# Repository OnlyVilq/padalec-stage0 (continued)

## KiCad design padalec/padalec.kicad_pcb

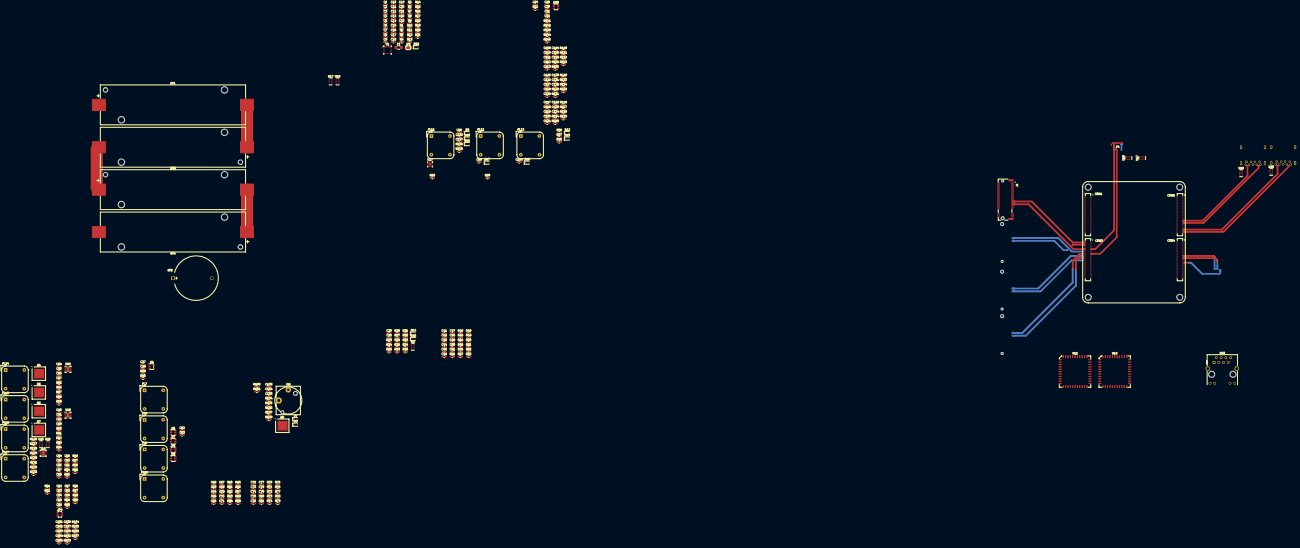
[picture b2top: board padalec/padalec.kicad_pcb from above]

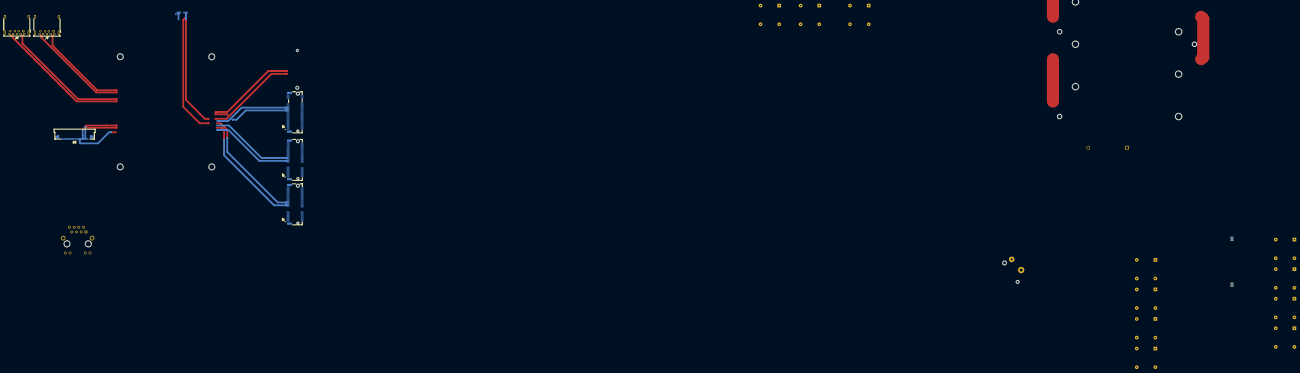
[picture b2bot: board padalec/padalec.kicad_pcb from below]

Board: 4 copper layers, 343 parts (6 on the bottom side), 225 nets.

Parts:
BT1, BT2, BT3, BT4: Battery_Cell; BatteryHolder_Keystone_1042_1x18650
BT5: Battery_Cell; BatteryHolder_MYOUNG_BS-07-A1BJ001_CR2032
C1, C2, C7, C8, C11, C13, C15, C22, C23, C25, C54, C55, C63, C73, C82, C83, C90, C94, C101, C102, C109, C110, C117, C118, C125, C126: 10u; C_0603_1608Metric_Pad1.08x0.95mm_HandSolder
C3, C6, C52, C53, C57, C61, C85, C89, C91, C95, C98, C99, C100, C104, C108, C112, C116, C120, C124, C128, C132: 0.1u; C_0603_1608Metric_Pad1.08x0.95mm_HandSolder
C4, C5: 47n; C_0603_1608Metric_Pad1.08x0.95mm_HandSolder
C9, C41: 1n; C_0603_1608Metric_Pad1.08x0.95mm_HandSolder
C10, C27, C28, C48, C50, C51: 4.7u; C_0603_1608Metric_Pad1.08x0.95mm_HandSolder
C12, C14, C17, C18, C19, C20, C21, C29, C62, C64, C72, C74, C134: 1u; C_0603_1608Metric_Pad1.08x0.95mm_HandSolder
C16, C26, C31, C42, C43, C44, C45, C49, C56, C65, C68, C69, C70, C71, C75, C78, C79, C80, C81, C84, C103, C111, C119, C127, C133, C135: 100n; C_0603_1608Metric_Pad1.08x0.95mm_HandSolder
C24: 10n; C_0603_1608Metric_Pad1.08x0.95mm_HandSolder
C30: 2.2n; C_0603_1608Metric_Pad1.08x0.95mm_HandSolder
C32: 22n; C_0603_1608Metric_Pad1.08x0.95mm_HandSolder
C46, C47: 6p; C_0603_1608Metric_Pad1.08x0.95mm_HandSolder
C58, C105, C113, C121, C129: 2.2u; C_0603_1608Metric_Pad1.08x0.95mm_HandSolder
C59, C60, C87, C88, C106, C107, C114, C115, C122, C123, C130, C131: 22u; C_0603_1608Metric_Pad1.08x0.95mm_HandSolder
C66, C67, C76, C77: 6.8p; C_0603_1608Metric_Pad1.08x0.95mm_HandSolder
C86: 3.3u; C_0603_1608Metric_Pad1.08x0.95mm_HandSolder
C92, C93, C96, C97: 150u; C_0603_1608Metric_Pad1.08x0.95mm_HandSolder
C136, C137: 220p; C_0603_1608Metric_Pad1.08x0.95mm_HandSolder
D2: eDP_30pin; Amphenol_F32Q-1A7x1-11029_1x29-1MP_P0.5mm_Horizontal
D7, D8, D9, D10, D11, D12, D13, D14, D15, D16, D17, D18: PESD5V0X1BL; D_SOD-323
F1: Fuse; Fuse_1206_3216Metric_Pad1.42x1.75mm_HandSolder
FL7, FL8, FL9, FL10: Choke_Schaffner_RN102-04-14.0x14.0mm
FL11, FL12, FL13, FL14, FL15, FL16, FL17: DNP; Choke_Schaffner_RN102-04-14.0x14.0mm
J1: CM3588 Hirose Connector; CM3588
J4, J6: Bus_M.2_Socket_M; AMPHENOL_MDT420M03001
J5, J9: Bus_M.2_Socket_E; AMPHENOL_MDT420E03001
J7, J8: USB3_A; USB3_A_Molex_48393-001
J10: HDMI_A; WDFN-10-1EP_3x3mm_P0.5mm_EP1.8x2.5mm
J11: AudioJack3_SwitchTR; Jack_6.35mm_Neutrik_NJ2FD-V_Vertical
JP1: SolderJumper_2_Open; SolderJumper-2_P1.3mm_Open_RoundedPad1.0x1.5mm
JP4: 5v buck; SOT-23-6
P1: USB_C_Plug; USB_C_Plug_Molex_105444
Q4, Q5, Q6, Q7, Q8: NMOS; Nordic_AQFN-94-1EP_7x7mm_P0.4mm
R1, R134: 2.2k; R_0603_1608Metric_Pad0.98x0.95mm_HandSolder
R2, R38, R145: R_Small; R_0603_1608Metric_Pad0.98x0.95mm_HandSolder
R3: 30.31 k; R_0603_1608Metric_Pad0.98x0.95mm_HandSolder
R4, R22: 100; R_0603_1608Metric_Pad0.98x0.95mm_HandSolder
R5, R7, R9, R10, R11, R47, R48, R49, R50, R54, R56, R59, R61, R62, R63, R64, R65, R66, R67, R68, R69, R71, R72, R73, R74, R75, R76, R77, R78, R79, R81, R82, R84, R86, R89, R100, R101, R102, R104, R107, R108, R110, R113, R114, R116, R119, R120, R122, R125, R135, R137, R138, R144: 10k; R_0603_1608Metric_Pad0.98x0.95mm_HandSolder
R6: 470k; R_0603_1608Metric_Pad0.98x0.95mm_HandSolder
R8, R20: 1k; R_0603_1608Metric_Pad0.98x0.95mm_HandSolder
R12, R13, R14, R15, R16: 68; R_0603_1608Metric_Pad0.98x0.95mm_HandSolder
R17: 1m; R_0603_1608Metric_Pad0.98x0.95mm_HandSolder
R18, R21, R45: 1M; R_0603_1608Metric_Pad0.98x0.95mm_HandSolder
R19: 4k5; R_0603_1608Metric_Pad0.98x0.95mm_HandSolder
R23, R29, R30, R31, R32, R33: DNP; R_0603_1608Metric_Pad0.98x0.95mm_HandSolder
R24, R25, R26, R27, R28, R34, R35, R36, R37: 33; R_0603_1608Metric_Pad0.98x0.95mm_HandSolder
R39, R80, R83: 47k; R_0603_1608Metric_Pad0.98x0.95mm_HandSolder
R40, R46, R51, R52, R53, R55, R85, R90, R91, R93, R94, R95, R96, R98, R99, R103, R109, R115, R121, R136, R143: 100k; R_0603_1608Metric_Pad0.98x0.95mm_HandSolder
R41: 4.7k; R_0603_1608Metric_Pad0.98x0.95mm_HandSolder
R42: 0; R_0603_1608Metric_Pad0.98x0.95mm_HandSolder
R43: 10K; R_0603_1608Metric_Pad0.98x0.95mm_HandSolder
R44: 12K; R_0603_1608Metric_Pad0.98x0.95mm_HandSolder
R57, R87, R105, R111, R117, R123: 20k; R_0603_1608Metric_Pad0.98x0.95mm_HandSolder
R58, R106, R112, R118, R124: 45.3k; R_0603_1608Metric_Pad0.98x0.95mm_HandSolder
R60, R70: 1; R_0603_1608Metric_Pad0.98x0.95mm_HandSolder
R88: 73.2k; R_0603_1608Metric_Pad0.98x0.95mm_HandSolder
R92, R97: 37.4k; R_0603_1608Metric_Pad0.98x0.95mm_HandSolder
R126, R127, R128, R129, R130, R131, R132, R133: 499; R_0603_1608Metric_Pad0.98x0.95mm_HandSolder
R139, R140: 2.2K; R_0603_1608Metric_Pad0.98x0.95mm_HandSolder
R141: dnp; R_0603_1608Metric_Pad0.98x0.95mm_HandSolder
R142: 10; R_0603_1608Metric_Pad0.98x0.95mm_HandSolder
U1: BQ25798; Texas_RQM0029A_VQFN-29_4x4mm_P0.4mm
U3, U17, U17#2, U18, U18#2, U19, U20, U25, U26: TPD6E05U06RVZ; Texas_R-PUSON-N14
U4: MCP73831-2-OT; SOT-23-5
U6, U7, U8, U9: 82400102; SOT-23-6
U10: TMJUTVW0021192448; RJ45_Hanrun_HR911105A_Horizontal
U12, U13: 9FGV0441; PLCC-44_16.6x16.6mm_P1.27mm
U15, U16: TPS2561; VSON-10-1EP_3x3mm_P0.5mm_EP1.65x2.4mm_ThermalVias
U27: FUSB302BMPX; WQFN-14-1EP_2.5x2.5mm_P0.5mm_EP1.45x1.45mm
U28: TPS22810DBV; SOT-23-6

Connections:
+1V8: R23.1, R134.1, R136.1
+3V3: C29.1, R38.1, R42.1, R139.1, R140.1, U27.3 (VDD), U27.4 (VDD), U28.1 (VIN)
+5V: C27.1, C90.1, C91.1, C94.1, C95.1, JP4.2 (B), R93.1, R94.1, R98.1, R99.1, U4.4 (V_{DD}), U15.2 (IN), U15.3 (IN), U16.2 (IN), U16.3 (IN), U27.12 (VCONN), U27.13 (VCONN)
/Debug UART/RX: D12.2 (A2), R37.2, R38.2
/Debug UART/TX: D13.2 (A2), R36.2
/Debug UART/UART2_RX: J1.22, R37.1
/Debug UART/UART2_TX: J1.20, R36.1
/EDP 1/Bl_VCC: C32.2, D2.26 (Bl_VCC), D2.27 (Bl_VCC), D2.28 (Bl_VCC), D2.29 (Bl_VCC), R144.2
/EDP 1/LCD_VCC: C31.1, D2.12 (LCD_VCC), D2.13 (LCD_VCC), R141.2, R142.1, U28.6 (VOUT)
/EDP 1/eDP.AUX_N: D2.10 (AUX_N), J1.359
/EDP 1/eDP.AUX_P: D2.9 (AUX_P), J1.357
/EDP 1/eDP.TX0_N: D2.6 (TX0_N), J1.347
/EDP 1/eDP.TX0_P: D2.7 (TX0_P), J1.345
/EDP 1/eDP.TX1_N: D2.3 (TX1_N), J1.341
/EDP 1/eDP.TX1_P: D2.4 (TX1_P), J1.339
/Ethernet/Gled: C52.1, J1.72
/Ethernet/TD1_N: J1.80, U6.3
/Ethernet/TD1_P: J1.78, U6.1
/Ethernet/TD2_N: J1.86, U7.3
/Ethernet/TD2_P: J1.84, U7.1
/Ethernet/TD3_N: J1.92, U8.3
/Ethernet/TD3_P: J1.90, U8.1
/Ethernet/TD4_N: J1.98, U9.3
/Ethernet/TD4_P: J1.96, U9.1
/Ethernet/U10_4: FL7.3, U6.4
/Ethernet/U10_6: FL7.1, U6.6
/Ethernet/U11_4: FL8.3, FL9.3, U7.4
/Ethernet/U11_6: FL8.1, FL9.1, U7.6
/Ethernet/U12_4: FL10.3, U8.4
/Ethernet/U12_6: FL10.1, U8.6
/Ethernet/Yled: C53.1, J1.74
/HDMI_tx/D0+: FL16.2, J10.7 (D0+), U25.9 (D3+)
/HDMI_tx/D0-: FL16.4, J10.9 (D0-), U25.8 (D3-)
/HDMI_tx/D1+: FL15.2, J10.4 (D1+), U25.12 (D2+)
/HDMI_tx/D1-: FL15.4, J10.6 (D1-), U25.11 (D2-)
/HDMI_tx/D2+: FL14.2, J10.1 (D2+), U25.14 (D1+)
/HDMI_tx/D2-: FL14.4, J10.3 (D2-), U25.13 (D1-)
/HDMI_tx/HDMI.D0_N: FL16.3, R128.1
/HDMI_tx/HDMI.D0_P: FL16.1, R129.1
/HDMI_tx/HDMI.D1_N: FL15.3, R130.1
/HDMI_tx/HDMI.D1_P: FL15.1, R131.1
/HDMI_tx/HDMI.D2_N: FL14.3, R132.1
/HDMI_tx/HDMI.D2_P: FL14.1, R133.1
/HDMI_tx/HDMI.D3_N: FL17.3, R126.1
/HDMI_tx/HDMI.D3_P: FL17.1, R127.1
/Jack_35/DET: R136.2, R137.1
/Jack_35/HPL: C133.1, D7.2 (A2), J1.104, J11.T, R135.1
/Jack_35/HPR: C135.1, D8.2 (A2), J1.103, R138.1
/Jack_35/HP_DET: J1.108, R134.2
/PCIE/M2_E_x1/3v3: J5.2 (3.3V), J5.4 (3.3V), J5.72 (3.3V), J5.74 (3.3V), R81.1, R82.1
/PCIE/M2_E_x1/~W_DISABLE1: J5.56 (~W_DISABLE1), R81.2
/PCIE/M2_E_x1/~W_DISABLE2: J5.54 (~W_DISABLE2), R82.2
/PCIE/M2_E_x2/3v3: J9.2 (3.3V), J9.4 (3.3V), J9.72 (3.3V), J9.74 (3.3V), R100.1, R101.1
/PCIE/M2_E_x2/~W_DISABLE1: J9.56 (~W_DISABLE1), R100.2
/PCIE/M2_E_x2/~W_DISABLE2: J9.54 (~W_DISABLE2), R101.2
/PCIE/M2_M_x1/3v3: J4.2 (3.3V), J4.4 (3.3V), J4.12 (3.3V), J4.14 (3.3V), J4.16 (3.3V), J4.18 (3.3V), J4.70 (3.3V), J4.72 (3.3V), J4.74 (3.3V), R80.1
/PCIE/M2_M_x2/3v3: J6.2 (3.3V), J6.4 (3.3V), J6.12 (3.3V), J6.14 (3.3V), J6.16 (3.3V), J6.18 (3.3V), J6.70 (3.3V), J6.72 (3.3V), J6.74 (3.3V), R83.1
/PCIE/PCIE CLOCK 0/CK_REF_FG: R62.2, R68.1
/PCIE/PCIE CLOCK 0/FG_OE_0: R64.2, U12.12 (~OE0)
/PCIE/PCIE CLOCK 0/FG_OE_1: R65.2, U12.17 (~OE1)
/PCIE/PCIE CLOCK 0/FG_OE_2: R66.2, U12.24 (~OE2)
/PCIE/PCIE CLOCK 0/FG_OE_3: R67.2, U12.29 (~OE3)
/PCIE/PCIE CLOCK 0/FG_SSEN: R63.2, R69.1, U12.32 (VSS_EN_TRI)
/PCIE/PCIE CLOCK 0/V1P8FG: C63.1, C65.1, C68.1, C69.1, C70.1, C71.1, R60.1, U12.4 (VDDXTAL), U12.5 (VDDREF), U12.9 (VDDDIG), U12.16 (VDDO), U12.25 (VDDO)
/PCIE/PCIE CLOCK 0/V1P8FGA: C62.1, C64.1, R60.2, U12.21 (VDDA)
/PCIE/PCIE CLOCK 0/VCC1P8: R61.1, R62.1, R63.1
/PCIE/PCIE CLOCK 1/CK_REF_FG: R72.2, R78.1
/PCIE/PCIE CLOCK 1/FG_OE_0: R74.2, U13.12 (~OE0)
/PCIE/PCIE CLOCK 1/FG_OE_1: R75.2, U13.17 (~OE1)
/PCIE/PCIE CLOCK 1/FG_OE_2: R76.2, U13.24 (~OE2)
/PCIE/PCIE CLOCK 1/FG_OE_3: R77.2, U13.29 (~OE3)
/PCIE/PCIE CLOCK 1/FG_SSEN: R73.2, R79.1, U13.32 (VSS_EN_TRI)
/PCIE/PCIE CLOCK 1/V1P8FG: C73.1, C75.1, C78.1, C79.1, C80.1, C81.1, R70.1, U13.4 (VDDXTAL), U13.5 (VDDREF), U13.9 (VDDDIG), U13.16 (VDDO), U13.25 (VDDO)
/PCIE/PCIE CLOCK 1/V1P8FGA: C72.1, C74.1, R70.2, U13.21 (VDDA)
/PCIE/PCIE CLOCK 1/VCC1P8: R71.1, R72.1, R73.1
/PCIE/Port_1.REFCLK_N: J1.260, U13.14 (~DIF0)
/PCIE/Port_1.REFCLK_P: J1.258, U13.13 (DIF0)
/RK3588/PWRON: C24.1, J1.17, R22.2
/RK3588/PortA.RXN: J1.206, J4.43 (PERp0/SATA-B-)
/RK3588/PortA.RXP: J1.204, J4.41 (PERn0/SATA-B+)
/RK3588/PortA.TXN: J1.224, J4.49 (PETp0/SATA-A+)
/RK3588/PortA.TXP: J1.222, J4.47 (PETn0/SATA-A-)
/RK3588/PortB.RXN: J1.212, J6.43 (PERp0/SATA-B-)
/RK3588/PortB.RXP: J1.210, J6.41 (PERn0/SATA-B+)
/RK3588/PortB.TXN: J1.230, J6.49 (PETp0/SATA-A+)
/RK3588/PortB.TXP: J1.228, J6.47 (PETn0/SATA-A-)
/RK3588/PortC.RXN: J1.236, J5.43 (PERn0)
/RK3588/PortC.RXP: J1.234, J5.41 (PERp0)
/RK3588/PortC.TXN: J1.248, J5.37 (PETn0)
/RK3588/PortC.TXP: J1.246, J5.35 (PETp0)
/RK3588/PortD.RXN: J1.242, J9.43 (PERn0)
/RK3588/PortD.RXP: J1.240, J9.41 (PERp0)
/RK3588/PortD.TXN: J1.254, J9.37 (PETn0)
/RK3588/PortD.TXP: J1.252, J9.35 (PETp0)
/RK3588/SD_0.CLK: J1.360, R34.1, R34.2, U3.11 (D2-)
/RK3588/SD_0.CMD: J1.356, R28.1, R28.2, R33.2, U3.12 (D2+)
/RK3588/SD_0.D0: J1.364, R24.1
/RK3588/SD_0.D1: J1.366, R25.1
/RK3588/SD_0.D2: J1.352, R26.1
/RK3588/SD_0.D3: J1.354, R27.1
/RK3588/SD_0.DET: J1.370, R23.2, R35.2
/RK3588/SD_0.VDD: C25.1, C26.1, D15.2 (A2), J1.358, R29.1, R30.1, R31.1, R32.1, R33.1
/RK3588/USB3_host_0.D_N: FL11.1, U17.13 (D1-)
/RK3588/USB3_host_0.D_P: FL11.3, U17.14 (D1+)
/RK3588/USB3_host_0.SBU1: P1.A8 (SBU1), U18.9 (D3+)
/RK3588/USB3_host_0.SBU2: P1.B8 (SBU2), U18.8 (D3-)
/RK3588/USB3_host_0.SCL: R140.2, U27.6 (SCL)
/RK3588/USB3_host_0.SDA: R139.2, U27.7 (SDA)
/RK3588/USB3_host_0.SSRX2_N: P1.A10 (RX2-), U18.13 (D1-)
/RK3588/USB3_host_0.SSRX2_P: P1.A11 (RX2+), U18.14 (D1+)
/RK3588/USB3_host_0.SSRX_N: J1.223, P1.B10 (RX1-), U17.11 (D2-)
/RK3588/USB3_host_0.SSRX_P: J1.221, P1.B11 (RX1+), U17.12 (D2+)
/RK3588/USB3_host_0.SSTX2_N: P1.B3 (TX2-), U18.11 (D2-)
/RK3588/USB3_host_0.SSTX2_P: P1.B2 (TX2+), U18.12 (D2+)
/RK3588/USB3_host_0.SSTX_N: J1.235, P1.A3 (TX1-), U17.8 (D3-)
/RK3588/USB3_host_0.SSTX_P: J1.233, P1.A2 (TX1+), U17.9 (D3+)
/RK3588/USB3_host_1.D_N: FL13.1, J1.198
/RK3588/USB3_host_1.D_P: FL13.3, J1.196
/RK3588/USB3_host_1.SSRX_N: J1.197, J8.5 (SSRX-)
/RK3588/USB3_host_1.SSRX_P: J1.195, J8.6 (SSRX+)
/RK3588/USB3_host_1.SSTX_N: J1.191, J8.8 (SSTX-)
/RK3588/USB3_host_1.SSTX_P: J1.189, J8.9 (SSTX+)
/RK3588/USBC_host_0.D_N: FL12.1, J1.192
/RK3588/USBC_host_0.D_P: FL12.3, J1.190
/RK3588/USBC_host_0.SSRX_N: J1.173, J7.5 (SSRX-)
/RK3588/USBC_host_0.SSRX_P: J1.171, J7.6 (SSRX+)
/RK3588/USBC_host_0.SSTX_N: J1.167, J7.8 (SSTX-)
/RK3588/USBC_host_0.SSTX_P: J1.165, J7.9 (SSTX+)
/RK3588/USB_external.EN1: J1.239, R90.1, U15.4 (EN1)
/RK3588/USB_external.EN2: J1.261, R95.1, U16.4 (EN1)
/RK3588/USB_external.EN3: J1.397, R96.1, U16.5 (EN2)
/RK3588/USB_external.~Fault1: R93.2, U15.10 (~FAULT1)
/RK3588/USB_external.~Fault2: R98.2, U16.10 (~FAULT1)
/RK3588/USB_external.~Fault3: R99.2, U16.6 (~FAULT2)
/USB-external/5v5_A0: C97.1, C99.2, D17.2 (A2), J7.1 (VBUS), U16.9 (OUT1)
/USB-external/5v5_C0: C93.1, C98.2, D11.2 (A2), P1.A4 (VBUS), P1.A9 (VBUS), P1.B4 (VBUS), P1.B9 (VBUS), U15.9 (OUT1), U27.2 (VBUS)
/USB-external/5v5_C1: C96.1, C100.2, D18.2 (A2), J8.1 (VBUS), U16.8 (OUT2)
/USB-external/Power switch/5v5_out_2: C92.1, U15.8 (OUT2)
/USB-external/Power switch/EN2: R91.1, U15.5 (EN2)
/USB-external/Power switch/~FAULT2: R94.2, U15.6 (~FAULT2)
/USB-external/USB 3.x C/CC1: C137.1, D10.2 (A2), P1.A5 (CC), U27.10 (CC1), U27.11 (CC1)
/USB-external/USB 3.x C/CC2: C136.1, D9.2 (A2), P1.B5 (VCONN), U27.1 (CC2), U27.14 (CC2)
/USB-internal/3v3: C42.1, C43.1, C44.1, C45.1, C48.1, C49.1, C50.1, C51.1, R41.1, R42.2, R47.2, R48.2, R49.2, R50.2, R52.1, R53.1
/USB-internal/vbus_det: C41.1, R41.2
/Zasilanie/Bat: BT1.1 (+), C22.1, C23.1, R4.1, R5.1, R8.1, R12.2, U1.22 (BAT), U1.23 (BAT)
/Zasilanie/REGN: C10.1, R1.1, R2.1, U1.5 (REGN)
/Zasilanie/SRN: R17.2, R18.2
/Zasilanie/VC0: C21.2, R16.1
/Zasilanie/VC1: C19.2, C20.1, R15.1
/Zasilanie/VC2: C18.2, C19.1, R14.1
/Zasilanie/VC3: C17.2, C18.1, R13.1
/Zasilanie/VC4: C17.1, R12.1
/Zasilanie/vsys: C13.1, C15.1, C16.1, JP1.1 (A), R11.1, U1.25 (SYS)
/microSD/DAT0: R24.2, R29.2, U3.9 (D3+)
/microSD/DAT1: R25.2, R30.2, U3.8 (D3-)
/microSD/DAT2: R26.2, R31.2, U3.14 (D1+)
/microSD/DAT3: R27.2, R32.2, U3.13 (D1-)
/microSD/DET_A: D14.2 (A2), R35.1
AGND: R59.2, R89.2, R107.2, R113.2, R119.2, R125.2
BGND: BT4.2 (-), C20.2, C21.1, R16.2, R17.1
GND: BT5.2 (-), C1.2, C2.2, C3.2, C6.2, C7.2, C8.2, C9.2, C10.2, C11.2, C12.1, C12.2, C13.2, C14.2, C15.2, C16.2, C22.2, C23.2, C24.2, C25.2, C26.2, C27.2, C28.2, C29.2, C30.2, C31.2, C41.2, C42.2, C43.2, C44.2, C45.2, C46.1, C47.1, C48.2, C49.2, C50.2, C51.2, C52.2, C53.2, C54.2, C55.2, C56.2, C59.2, C60.2, C61.2, C62.2, C63.2, C64.2, C65.2, C66.1, C67.1, C68.2, C69.2, C70.2, C71.2, C72.2, C73.2, C74.2, C75.2, C76.1, C77.1, C78.2, C79.2, C80.2, C81.2, C82.2, C83.2, C84.2, C87.2, C88.2, C89.2, C90.2, C91.2, C92.2, C93.2, C94.2, C95.2, C96.2, C97.2, C98.1, C99.1, C100.1, C101.2, C102.2, C103.2, C106.2, C107.2, C108.2, C109.2, C110.2, C111.2, C114.2, C115.2, C116.2, C117.2, C118.2, C119.2, C122.2, C123.2, C124.2, C125.2, C126.2, C127.2, C130.2, C131.2, C132.2, C134.2, C136.2, C137.2, D2.2 (Hs_GND), D2.5 (Hs_GND), D2.8 (Hs_GND), D2.11 (Hs_GND), D2.15 (Hs_GND), D2.16 (Hs_GND), D2.18 (Bl_GND), D2.19 (Bl_GND), D2.20 (Bl_GND), D2.21 (Bl_GND), D7.1 (A1), D8.1 (A1), D9.1 (A1), D10.1 (A1), D11.1 (A1), D12.1 (A1), D13.1 (A1), D14.1 (A1), D15.1 (A1), D16.1 (A1), D17.1 (A1), D18.1 (A1), J1.11, J1.12, J1.13, J1.24, J1.33, J1.34, J1.39, J1.40, J1.45, J1.46, J1.51, J1.52, J1.57, J1.58, J1.63, J1.64, J1.69, J1.70, J1.73, J1.76, J1.77, J1.82, J1.88, J1.91, J1.94, J1.100, J1.121, J1.127, J1.133, J1.139, J1.145, J1.151, J1.157, J1.163, J1.169, J1.175, J1.181, J1.187, J1.193, J1.199, J1.201, J1.207, J1.213, J1.219, J1.225, J1.231, J1.237, J1.331, J1.337, J1.343, J1.349, J1.355, J1.361, J4.1 (GND), J4.3 (GND), J4.9 (GND), J4.15 (GND), J4.21 (GND), J4.27 (GND), J4.33 (GND), J4.39 (GND), J4.45 (GND), J4.51 (GND), J4.57 (GND), J4.71 (GND), J4.73 (GND), J4.75 (GND), J5.1 (GND), J5.7 (GND), J5.18 (GND), J5.33 (GND), J5.39 (GND), J5.45 (GND), J5.51 (GND), J5.57 (GND), J5.63 (GND), J5.69 (GND), J5.75 (GND), J6.1 (GND), J6.3 (GND), J6.9 (GND), J6.15 (GND), J6.21 (GND), J6.27 (GND), J6.33 (GND), J6.39 (GND), J6.45 (GND), J6.51 (GND), J6.57 (GND), J6.71 (GND), J6.73 (GND), J6.75 (GND), J7.4 (GND), J7.7 (DRAIN), J7.SH (SHIELD), J8.4 (GND), J8.7 (DRAIN), J8.SH (SHIELD), J9.1 (GND), J9.7 (GND), J9.18 (GND), J9.33 (GND), J9.39 (GND), J9.45 (GND), J9.51 (GND), J9.57 (GND), J9.63 (GND), J9.69 (GND), J9.75 (GND), P1.A1 (GND), P1.A12 (GND), P1.B1 (GND), P1.B12 (GND), P1.SH (SHIELD), R3.2, R6.2, R7.2, R10.2, R11.2, R21.2, R39.2, R40.2, R43.1, R44.1, R46.2, R51.2, R54.2, R56.2, R64.1, R65.1, R66.1, R67.1, R68.2, R69.2, R74.1, R75.1, R76.1, R77.1, R78.2, R79.2, R84.2, R86.2, R90.2, R91.2, R92.2, R95.2, R96.2, R97.2, R102.2, R104.2, R108.2, R110.2, R114.2, R116.2, R120.2, R122.2, R142.2, U1.10 (ACDRV2), U1.11 (ACDRV1), U1.27 (GND), U3.5 (GND), U3.10 (GND), U4.2 (V_{SS}), U6.2, U7.2, U8.2, U9.2, U12.1 (GNDXTAL), U12.7 (GNDREF), U12.8 (GNDDIG), U12.15 (GND), U12.20 (GNDA), U12.26 (GND), U12.30 (GND), U12.33 (EPAD), U12.34 (EPAD), U12.35 (EPAD), U12.36 (EPAD), U13.1 (GNDXTAL), U13.7 (GNDREF), U13.8 (GNDDIG), U13.15 (GND), U13.20 (GNDA), U13.26 (GND), U13.30 (GND), U13.33 (EPAD), U13.34 (EPAD), U13.35 (EPAD), U13.36 (EPAD), U15.1 (GND), U15.11 (PAD), U16.1 (GND), U16.11 (PAD), U17.5 (GND), U17.10 (GND), U18.5 (GND), U18.10 (GND), U25.5 (GND), U25.10 (GND), U27.8 (GND), U27.9 (GND), U27.15 (GND), U28.2 (GND)
GNDA: C133.2, C135.2, J1.102, J11.S, R135.2, R138.2
unnamed: BT1.2 (-), BT2.1 (+), R13.2
unnamed: BT2.2 (-), BT3.1 (+), R14.2
unnamed: BT3.2 (-), BT4.1 (+), R15.2
unnamed: BT5.1 (+), C28.1, U4.3 (V_{BAT})
unnamed: C58.1, R57.2
unnamed: C86.1, R87.2
unnamed: C105.1, R105.2
unnamed: C113.1, R111.2
unnamed: C121.1, R117.2
unnamed: C129.1, R123.2
unnamed: C1.1, C2.1, C3.1, D16.2 (A2), F1.2, U1.2 (VBUS), U1.3 (VBUS), U1.8 (VAC2), U1.9 (VAC1)
unnamed: J1.302, J1.308, J1.314
unnamed: J1.350, J1.362, J1.368
unnamed: FL12.4, J7.3 (D+)
unnamed: FL12.2, J7.2 (D-)
unnamed: FL13.4, J8.3 (D+)
unnamed: FL13.2, J8.2 (D-)
unnamed: C59.1, C60.1, C61.1, R57.1, R58.1
unnamed: C87.1, C88.1, C89.1, JP4.1 (A), R87.1, R88.1
unnamed: C106.1, C107.1, C108.1, R105.1, R106.1
unnamed: C114.1, C115.1, C116.1, R111.1, R112.1
unnamed: C122.1, C123.1, C124.1, R117.1, R118.1
unnamed: C130.1, C131.1, C132.1, R123.1, R124.1
unnamed: FL11.4, P1.A6 (D+)
unnamed: FL11.2, P1.A7 (D-)
unnamed: R18.1, R19.2
unnamed: R20.2, R21.1
unnamed: R126.2, R127.2
unnamed: R128.2, R129.2
unnamed: R130.2, R131.2
unnamed: R132.2, R133.2
unnamed: C134.1, R137.2
unnamed: C32.1, R143.2, R144.1
unnamed: R4.2, U1.18 (BATP)
unnamed: C4.1, U1.4 (BTST1)
unnamed: C5.2, U1.19 (BTST2)
unnamed: C6.1, C7.1, C8.1, C11.1, U1.29 (PMID)
unnamed: C9.1, U1.24 (SDRV)
unnamed: C4.2, U1.28 (SW1)
unnamed: C5.1, U1.26 (SW2)
unnamed: R2.2, R3.1, U1.16 (TS)
unnamed: C14.1, R8.2
unnamed: R39.1, U4.5 (PROG)
unnamed: C46.2, R45.1
unnamed: C47.2, R45.2
unnamed: C58.2, R58.2, R59.1
unnamed: C67.2, U12.3 (X2)
unnamed: C66.2, U12.2 (XIN/CLKIN_25)
unnamed: C77.2, U13.3 (X2)
unnamed: C76.2, U13.2 (XIN/CLKIN_25)
unnamed: C86.2, R88.2, R89.1
unnamed: R92.1, U15.7 (ILM)
unnamed: R97.1, U16.7 (ILM)
unnamed: C105.2, R106.2, R107.1
unnamed: C113.2, R112.2, R113.1
unnamed: C121.2, R118.2, R119.1
unnamed: C129.2, R124.2, R125.1
unnamed: FL17.2, U26.14 (D1+)
unnamed: FL17.4, U26.13 (D1-)
unnamed: U26.5 (GND), U26.10 (GND)
unnamed: C30.1, U28.4 (CT)
unnamed: R141.1, U28.5 (QOD)
VBUS: C54.1, C55.1, C56.1, C82.1, C83.1, C84.1, C101.1, C102.1, C103.1, C109.1, C110.1, C111.1, C117.1, C118.1, C119.1, C125.1, C126.1, C127.1, J1.1, J1.2, J1.3, J1.4, J1.5, J1.6, J1.7, J1.8, J1.9, J1.10, JP1.2 (B), R55.1, R85.1, R103.1, R109.1, R115.1, R121.1, R143.1, U6.5, U7.5, U8.5, U9.5

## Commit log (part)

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2026-03-25 dupa
